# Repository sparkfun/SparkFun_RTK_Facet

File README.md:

SparkFun RTK Facet
========================================

<table class="table table-hover table-striped table-bordered">
  <tr align="center">
   <td></td>
   <td></td>
  <tr align="center">
    <td><a href="https://www.sparkfun.com/products/20000">SparkFun RTK Facet L-Band (GPS-20000)</a></td>
    <td><a href="https://www.sparkfun.com/products/19029">SparkFun RTK Facet (GPS-19029)</a></td>
  </tr>
</table>

The SparkFun RTK Facet and RTK Facet L-Band are your one stop shop for high precision geolocation and surveying needs. For basic users, it’s incredibly easy to get up and running and for advanced users, the RTK Facet is a flexible and powerful tool. With just a few minutes of setup, the RTK Facet is one of the fastest ways to take centimeter grade measurements. By connecting your phone to the RTK Facet over Bluetooth, your phone can act as the radio link to provide correction data as well as receive the NMEA output from the device. This is exactly how $10,000 surveying devices have been operating for the past decade - we just made it easier, smaller, and a lot cheaper. 

The RTK Facet L-Band utilizes corrections from u-blox's PointPerfect service broadcast from a geosynchronous Inmarsat satellite. The only setup required is a WiFi SSID and password. Once entered, the device will provision itself and periodically (once a month) update the decryption keys necessary to use the PointPerfect service. The price of the RTK Facet L-Band includes a 12-month subscription. Additional years of service can be purchased.

Under the hood of the SparkFun RTK Facet is an ESP32 WROOM connected to a ZED-F9P as well as some peripheral hardware (OLED, LiPo fuel gauge, microSD, etc). Additionally, housed under the dome of the RTK Facet is a surveyor grade L1/L2 antenna. It is the same element found within our GNSS Multi-Band L1/L2 Surveying Antenna.

Under the hood of the SparkFun RTK Facet L-Band is an ESP32 WROOM connected to a ZED-F9P GNSS receiver, a NEO-D9S L-Band receiver (for corrections), and a variety of peripheral hardware (LiPo fuel gauge, microSD, etc). Additionally, housed under the dome of the RTK Facet L-Band is a surveyor grade L1/L2/L-Band antenna. This antenna is a unique combination of elements designed to receive the GNSS signals (L1/L2) alongside the 1.55GHz PointPerfect corrections. The built-in antenna has an ARP of 69mm from the base to the measuring point of the L1 antenna and an ARP of 68mm to the measuring point of the L2 antenna. The RTK Facet L-Band is programmed in Arduino and can be tailored by you to fit whatever your needs may be.

Repository Contents
-------------------

* **/Documents** - Datasheets and additional product information
* **/Hardware** - Eagle PCB files
* **/Labels** - Display overlay and info stickers
* **/Mechanical** - Drawings use to created injection molding tooling

Documentation
--------------

* **[RTK Product Manual](https://docs.sparkfun.com/SparkFun_RTK_Firmware/)** - A detailed guide describing all the various software features of the RTK product line. Essentially it is a manual for the firmware used by the RTK Facet.
* **[RTK Facet L-Band Hookup Guide](https://learn.sparkfun.com/tutorials/sparkfun-rtk-facet-l-band-hookup-guide)** - Hookup guide for the SparkFun RTK Facet L-Band.
* **[RTK Facet Hookup Guide](https://learn.sparkfun.com/tutorials/sparkfun-rtk-facet-hookup-guide)** - Hookup guide for the SparkFun RTK Facet.

License Information
-------------------

This product is _**open source**_! 

Please review the LICENSE.md file for license information. 

If you have any questions or concerns on licensing, please contact technical support on our [SparkFun forums](https://forum.sparkfun.com/viewforum.php?f=152).

Distributed as-is; no warranty is given.

- Your friends at SparkFun.

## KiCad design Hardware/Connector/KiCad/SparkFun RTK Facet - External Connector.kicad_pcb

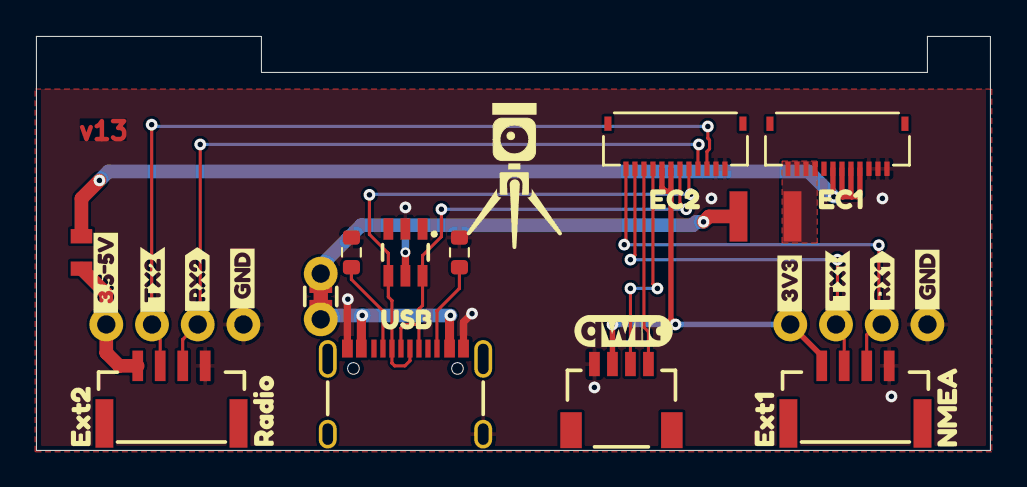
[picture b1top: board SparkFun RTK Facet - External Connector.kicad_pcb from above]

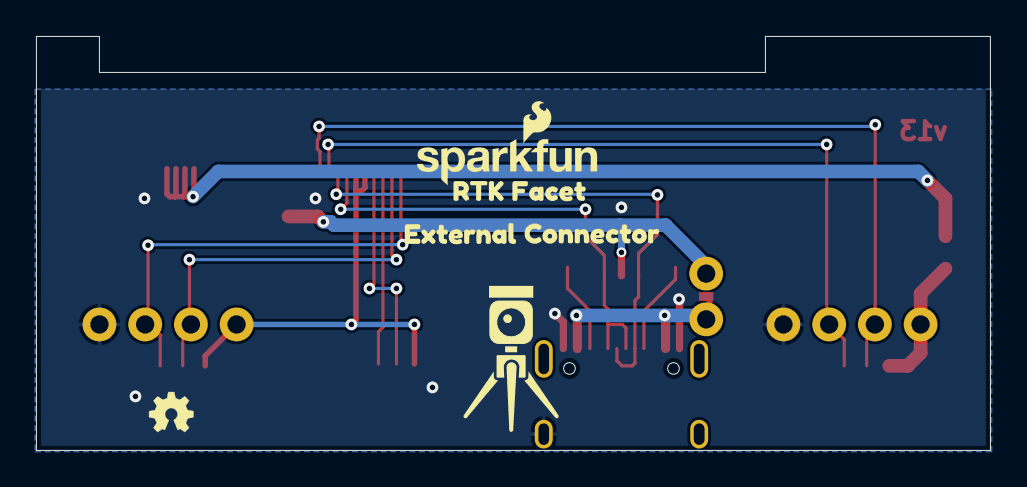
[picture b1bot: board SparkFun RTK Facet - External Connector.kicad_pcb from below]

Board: 4 copper layers, 53.0 x 23.0 mm, 37 parts (6 on the bottom side), 17 nets.

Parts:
D1: DT1042-04SO; SOT23-6
F1: 6V/0.5A/1A; 0805
F3: 6V/2.0A/4.0A; 1210
G3: OSHW_Logo; Creative_Commons_License
J1, J3: Conn_01x12_FPC_0.5mm; FPC_0.5mm-12
J2, J9: JST_Locking_4; JST_SMD_1.25mm-4_Locking
J4: Qwiic; JST_SMD_1.0mm-4_RA
J5: USB_C_Receptacle; USB-C_16
J11, J12: Conn_01x04; 1x04
JP0: Measure; Jumper_2_PTH_SMD_Combo-NC
LOGO1: OSHW-LOGOMINI; OSHW_Logo_2.5mm
LOGO2: SFE_LOGO_NAME_FLAME.1_INCH; SparkFun_Logo_10mm
R16, R17: 5.1k; R_0603_1608Metric
Ref**: Val**; SparkFun_RTK_20mm
Ref**#2: Val**; SparkFun_RTK_20mm
kibuzzard-66F4BFD6: G***; kibuzzard-66F4BFD6
kibuzzard-66F4BFE6: G***; kibuzzard-66F4BFE6
kibuzzard-66F4BFEC: G***; kibuzzard-66F4BFEC
kibuzzard-66F4C0A3: G***; kibuzzard-66F4C0A3
kibuzzard-66F4C0CF: G***; kibuzzard-66F4C0CF
kibuzzard-66F4C0D4: G***; kibuzzard-66F4C0D4
kibuzzard-66F4C0DF: G***; kibuzzard-66F4C0DF
kibuzzard-66F4C0F8: G***; kibuzzard-66F4C0F8
kibuzzard-66F4C0FC: G***; kibuzzard-66F4C0FC
kibuzzard-66F4C1AD: G***; kibuzzard-66F4C1AD
kibuzzard-66F4C03C, kibuzzard-66F4C03C#2: G***; kibuzzard-66F4C03C
kibuzzard-66F4C09A: G***; kibuzzard-66F4C09A
kibuzzard-66F4C18F: G***; kibuzzard-66F4C18F
kibuzzard-66F4C088: G***; kibuzzard-66F4C088
kibuzzard-66F4C143: G***; kibuzzard-66F4C143
kibuzzard-66F4C147: G***; kibuzzard-66F4C147
kibuzzard-66F4C199: G***; kibuzzard-66F4C199

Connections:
3.3V: J2.1, J3.7, J3.8, J4.2, J12.4
ESP_21/SDA: J3.9, J4.3
ESP_22/SCL: J3.10, J4.4
EXTERNAL_SERIAL1_RXI: J2.3, J3.12, J12.2
EXTERNAL_SERIAL1_TXO: J2.2, J3.11, J12.3
GND: D1.2 (GND), J1.1, J1.2, J1.3, J2.4, J3.1, J3.2, J4.1, J5.GND, J5.S (SHIELD), J9.4, J11.1, J12.1, R16.2, R17.2
unnamed: D1.5 (VCC), F3.2, JP0.2 (B)
unnamed: J5.A5 (CC1), R17.1
unnamed: J5.B5 (CC2), R16.1
unnamed: F1.2, J9.1, J11.4
unnamed: J5.VBUS, JP0.1 (A)
USB_DM: D1.4 (I/O3), J3.5, J5.A7 (D-), J5.B7 (D-)
USB_DP: D1.6 (I/O4), J3.6, J5.A6 (D+), J5.B6 (D+)
V_BATT: F1.1, J1.4, J1.5, J1.6, J1.7
V_USB: F3.1, J1.9, J1.10, J1.11, J1.12
ZED-RXI2: J3.4, J9.3, J11.2
ZED-TXO2: J3.3, J9.2, J11.3

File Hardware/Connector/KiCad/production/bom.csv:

Designator,Footprint,Quantity,Value,LCSC Part #
D1,SOT23-6,1,DT1042-04SO,
F1,0805,1,6V/0.5A/1A,
F3,1210,1,6V/2.0A/4.0A,
"J1, J3",FPC_0.5mm-12,2,Conn_01x12_FPC_0.5mm,
"J11, J12",1x04,2,Conn_01x04,
"J2, J9",JST_SMD_1.25mm-4_Locking,2,JST_Locking_4,
J4,JST_SMD_1.0mm-4_RA,1,Qwiic,
J5,USB-C_16,1,USB_C_Receptacle,
JP0,Jumper_2_PTH_SMD_Combo-NC,1,Measure,
"R16, R17",0603,2,5.1k,

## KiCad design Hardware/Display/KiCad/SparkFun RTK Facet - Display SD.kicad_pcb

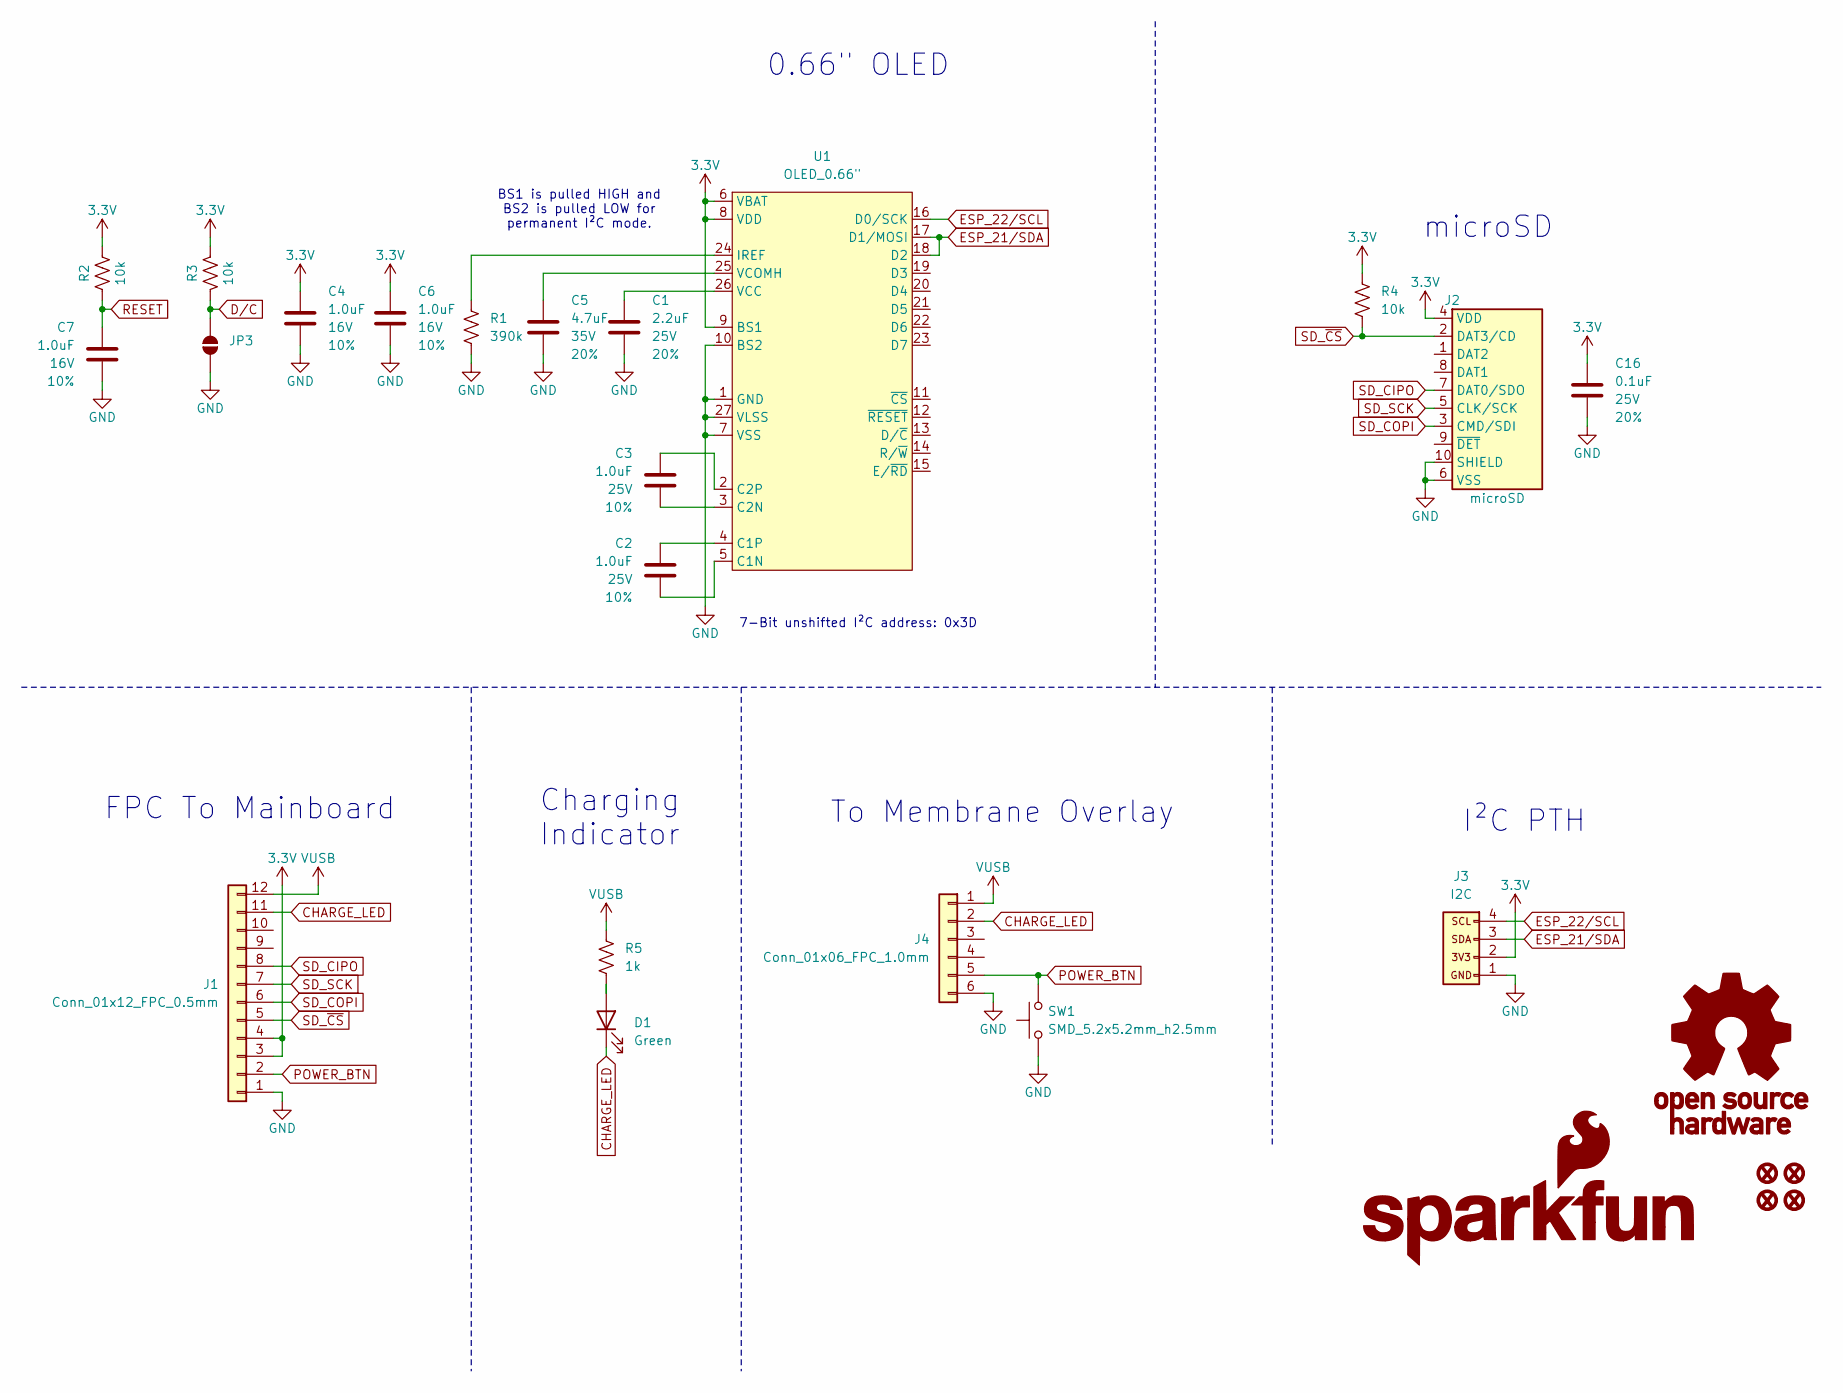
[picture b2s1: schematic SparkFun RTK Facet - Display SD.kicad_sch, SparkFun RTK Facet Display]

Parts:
C1: 2.2uF; C_0805_2012Metric; Voltage 25V; Tolerance 20%
C2, C3: 1.0uF; C_0805_2012Metric; Voltage 25V; Tolerance 10%
C4, C6, C7: 1.0uF; C_0603_1608Metric; Voltage 16V; Tolerance 10%
C5: 4.7uF; C_0603_1608Metric; Voltage 35V; Tolerance 20%
C16: 0.1uF; C_0603_1608Metric; Voltage 25V; Tolerance 20%
D1: Green; LED_1206_Bottom_Green
FID1, FID2, FID3, FID4: Fiducial_0.5mm; Fiducial_0.5mm_Mask1mm
G1: SparkFun_Logo
G2: OSHW_Logo; Creative_Commons_License
J1: Conn_01x12_FPC_0.5mm; FPC_0.5mm-12
J2: microSD; microSD_External_Pin
J3: I2C; 1x04
J4: Conn_01x06_FPC_1.0mm; FPC_1.0mm-6_LIF
JP3: Jumper_2_NO
R1: 390k; R_0603_1608Metric
R2, R3, R4: 10k; R_0603_1608Metric
R5: 1k; R_0402_1005Metric
SW1: SMD_5.2x5.2mm_h2.5mm; Push_SMD_5.2x5.2mm_h2.5mm
U1: OLED_0.66"; OLED_0.66-SMD

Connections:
3.3V: C4.1, C6.1, C16.1, J1.3, J1.4, J2.4 (VDD), J3.2, R2.2, R3.1, R4.1, U1.6 (VBAT), U1.8 (VDD), U1.9 (BS1)
CHARGE_LED: D1.1 (K), J1.11, J4.2
D/C: JP3.2 (B), R3.2
ESP_21/SDA: J3.3, U1.17 (D1/MOSI), U1.18 (D2)
ESP_22/SCL: J3.4, U1.16 (D0/SCK)
GND: C1.2, C4.2, C5.2, C6.2, C7.2, C16.2, J1.1, J2.6 (VSS), J2.10 (SHIELD), J3.1, J4.6, JP3.1 (A), R1.2, SW1.1, U1.1 (GND), U1.7 (VSS), U1.10 (BS2), U1.27 (VLSS), U1.28 (GND)
unnamed: D1.2 (A), R5.2
unnamed: C2.2, U1.5 (C1N)
unnamed: C2.1, U1.4 (C1P)
unnamed: C3.2, U1.3 (C2N)
unnamed: C3.1, U1.2 (C2P)
unnamed: R1.1, U1.24 (IREF)
unnamed: C1.1, U1.26 (VCC)
unnamed: C5.1, U1.25 (VCOMH)
POWER_BTN: J1.2, J4.5, SW1.2
RESET: C7.1, R2.1
SD_CIPO: J1.8, J2.7 (DAT0/SDO)
SD_COPI: J1.6, J2.3 (CMD/SDI)
SD_SCK: J1.7, J2.5 (CLK/SCK)
SD_~CS: J1.5, J2.2 (DAT3/CD), R4.2
VUSB: J1.12, J4.1, R5.1

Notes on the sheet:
7-Bit unshifted I²C address: 0x3D
BS1 is pulled HIGH and BS2 is pulled LOW for permanent I²C mode.
0.66" OLED
To Membrane Overlay
I²C PTH
FPC To Mainboard
Charging Indicator
microSD

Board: 2 copper layers, 38 parts (27 on the bottom side), 21 nets, no tracks yet.

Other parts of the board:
Ref**: Val**; SparkFun_RTK_20mm
Ref**#2: Val**; OSHW_Logo_5mm
kibuzzard-66E8FA3C: G***; kibuzzard-66E8FA3C
kibuzzard-66E8FA6A: G***; kibuzzard-66E8FA6A
kibuzzard-66E8FA6F: G***; kibuzzard-66E8FA6F
kibuzzard-66E8FA7A: G***; kibuzzard-66E8FA7A
kibuzzard-66E8FA21: G***; kibuzzard-66E8FA21
kibuzzard-66E8FA52: G***; kibuzzard-66E8FA52
kibuzzard-66E8FA75: G***; kibuzzard-66E8FA75
kibuzzard-66E8FB1B: G***; kibuzzard-66E8FB1B
kibuzzard-66E8FB47: G***; kibuzzard-66E8FB47
kibuzzard-66E8FBC7: G***; kibuzzard-66E8FBC7

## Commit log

2021-02-05 Add 22ohm to USB hub D+/D-.
2021-02-11 Fix errors on all 3 boards after enclosure review.
    * Flip connector board completely. Mirror connectors.
    * Mirror connector on SD board
    * Move LED above SIM socket
    * Add membrane connector to SD board
    * Remove switch connector from main board
    * Increase width of connector board, 2mm on each side - 54mm wide
2021-02-11 Add ignore. Mvoe hardware files into sub directory.
2021-02-16 Move display connector to side so overlay connector can be center. Notch PCBs. Add dummy PCB height. Add dummy retention plate.
2021-02-16 Adjust top edges for alignment.
2021-02-22 Update PROD ID on 12 pin connector. Add gerbers for v10.
2021-02-22 Moved power LED to left side of front display.
2021-02-28 Update Retention Plate design as per current Fusion model
2021-05-13 Create retention plate
2021-05-13 Adding bits for overlay creation
2021-05-13 Removing duplicate retention plate.
2021-05-13 Adding retention plate
2021-05-13 Add prelim cellular design
2021-05-14 Move external connectors to button control. Add radio connector. Move ESP32 to VOUT. Move USB to VOUT. Remove USB from I2C.
2021-05-14 Net rename to indicate inputs vs outputs
2021-05-14 Add dimensions
2021-05-14 Move overlay connector further down. Invert overlay connector pins.
2021-05-14 Move into sub directories
2021-05-14 Increase height 2mm to 23. Move OLED connector up 1mm. Move overlay connector down.
2021-05-14 Update silk
2021-05-14 Change to NO jumper for I2C pullups
2021-05-14 Increase external connector board height to 23mm.
2021-05-14 Double up 3.3V on cell connector. Create dummy test board.
2021-05-14 Double up 3.3V rail on Radio connector.
2021-05-14 v11 External Connector Gerbers
2021-05-14 Add gerbers for v11 Display board
2021-05-14 Gerbers for v11 main board
2021-05-14 Add retention plate gerbers v10
2021-06-22 Add overlays
2021-06-22 Adding production panels.
2021-06-25 Change connector panel orientation.
2021-08-30 Change to push push socket on cellular board.
2021-08-30 Change to external pins SD socket on display board.
2021-08-30 Add production panel for Display v13 PCB.
2021-09-23 Add route out. Panel files for v11.
2021-09-23 Add impedance control note to mainboard
2021-10-01 Paul edits. Move dummy to sub-folder
2021-10-01 Add Buzzard text
2021-10-04 Add cellular board production files
2021-10-05 Add r2 labels (SMA fixes). Restructure folders.
2021-11-22 Reduce Main, Connector, Display, and Cell board widths by 1mm to allow for v-score protrusion.
2021-12-03 Add revisions to schematics. Add PDFs of schematics.
2021-12-03 Remove old files
2021-12-14 Add Mechanicals
    - Make Directory "Mechanical"
    - Add PDF Drawings
    - Add Fusion Archive
    - Add Meshes and Solid for all parts designed in house
2021-12-14 Rename readme.md to README.md
2021-12-15 Create README.md
    Initial ReadMe according to SFE Template guidelines
2021-12-15 Update readme. Add firmware note.
2021-12-20 Move thermistor from heat sources.
2021-12-20 Update ESP32 to larger FP.
2021-12-20 Adjust ESP32 FP.
2022-01-03 Add panel files for main v12, connector v12, display v14
2022-01-03 Update WiFi overlay
2022-02-03 Update issue templates
2022-02-24 Extend retention plate length to make it reversible. Add LTE only sticker.
2022-04-08 Add 915MHz label
2022-04-08 Move to LIF overlay connector.
2022-04-11 Change to LIF 6 pin connector, remove GND plane around accel.
2022-05-18 Add LBand stickers
2022-05-19 v15 panel files. Add tCream to LIF.
2022-05-19 Add tCream to LIF connector on display board v15
2022-05-19 Add IDs to schematic
2022-06-09 Add L-Band main board
2022-06-15 Add I2C addresses to schematics
2022-08-30 Add I2C test header to display board - v1.6
2023-06-22 Fix product manual link
2023-08-24 Sticker: Update Facet ARP
2023-08-24 Facet v13: change charger IC FP, discrete 33s, change cream on ESP32.
2023-08-24 Remove silk from around the accel FP for DFM.
2023-08-24 Remove R1, change charger FP, change 33 discretes, ESP32 DFM paste.
2023-08-25 Close jumpers between ZED/NEO. Change resistor IDs to indicate L-Band Direct.
2023-08-25 Add v14 panel
2023-09-01 Update ID resistors.
2023-09-01 Update ID resistors
2024-09-26 Convert connector and display boards to KiCad
2024-09-26 Fix part number on LIF
2024-10-02 Add route out text
2024-10-02 Add DRC exclusions
2024-10-02 Add PDF and ZIP

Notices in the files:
parts and their libraries:
Released under the Creative Commons Attribution Share-Alike 4.0 License
https://creativecommons.org/licenses/by-sa/4.0
